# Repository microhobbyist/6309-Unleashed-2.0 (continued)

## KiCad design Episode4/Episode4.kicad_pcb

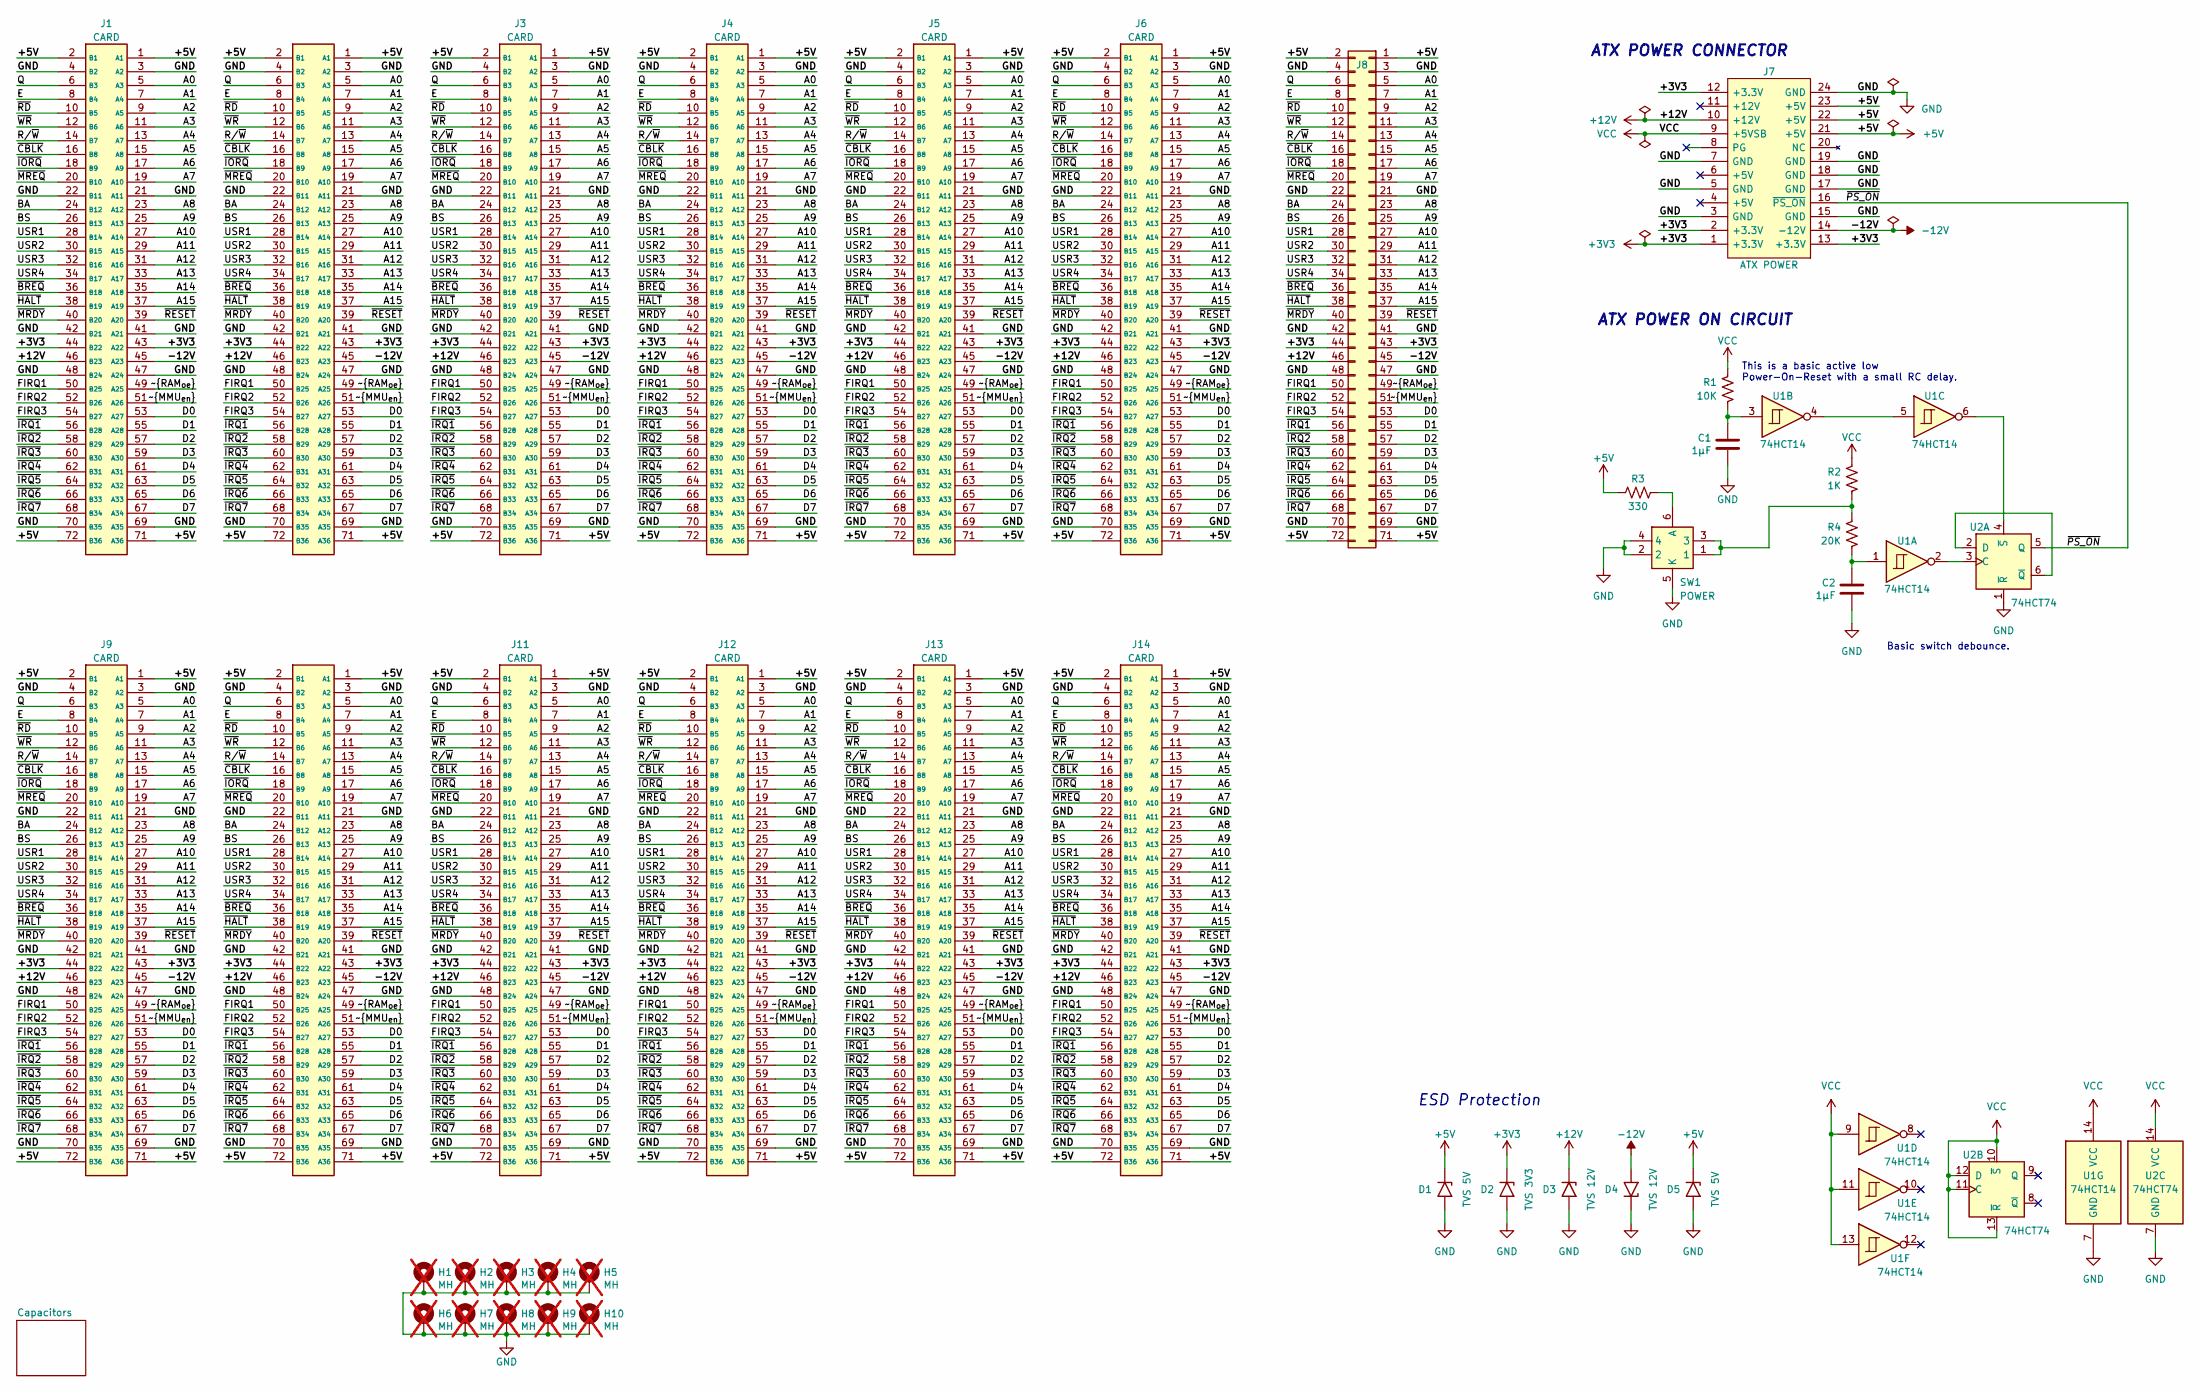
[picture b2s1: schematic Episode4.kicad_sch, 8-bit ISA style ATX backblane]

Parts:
C1, C2: 1µF; C_0805_2012Metric_Pad1.18x1.45mm_HandSolder; Manufacturer_Part_Number CL21B105KBFNNNG
D1, D5: TVS 5V; D_SMB; Manufacturer_Part_Number SMBJ5.0A-E3/5B
D2: TVS 3V3; D_SMB; Manufacturer_Part_Number SMBJ3V3-E3/5B
D3, D4: TVS 12V; D_SMB; Manufacturer_Part_Number SMBJ12A-E3/5B
H1, H2, H3, H4, H5, H6, H7, H8, H9, H10: MH; MountingHole_3.5mm_Pad_Via; not fitted
J1, J2, J3, J4, J5, J6, J9, J10, J11, J12, J13, J14: CARD; 72-pin CE connector; Mouser Part Number 571-5530843-8
J7: ATX POWER; ATX_PSU_CONN; Mouser Part Number 571-1-1775099-3
J8: BB Con; PinSocket_2x36_P2.54mm_Vertical; Manufacturer_Part_Number 929852-01-36-RA
R1: 10K; R_0805_2012Metric_Pad1.20x1.40mm_HandSolder; Manufacturer_Part_Number CR0805-FX-1002ELF
R2: 1K; R_0805_2012Metric_Pad1.20x1.40mm_HandSolder; Manufacturer_Part_Number CR0805-FX-1001ELF
R3: 330; R_0805_2012Metric_Pad1.20x1.40mm_HandSolder; Manufacturer_Part_Number CR0805-FX-3300ELF
R4: 20K; R_0805_2012Metric_Pad1.20x1.40mm_HandSolder; Manufacturer_Part_Number CR0805-FX-2002ELF
SW1: POWER; TS2912121G300D; Manufacturer_Part_Number TS29-1212-1-G-300-D; Mouser Part Number 179-TS2912121G300D
U1: 74HCT14; SOIC-14_3.9x8.7mm_P1.27mm; Manufacturer_Part_Number CD74HCT14M96
U2: 74HCT74; SOIC-14_3.9x8.7mm_P1.27mm; Manufacturer_Part_Number CD74HCT74M96

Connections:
+3V3: D2.1 (A1), J1.43 (A22), J1.44 (B22), J2.43 (A22), J2.44 (B22), J3.43 (A22), J3.44 (B22), J4.43 (A22), J4.44 (B22), J5.43 (A22), J5.44 (B22), J6.43 (A22), J6.44 (B22), J7.1 (+3.3V), J7.2 (+3.3V), J7.12 (+3.3V), J7.13 (+3.3V), J8.43, J8.44, J9.43 (A22), J9.44 (B22), J10.43 (A22), J10.44 (B22), J11.43 (A22), J11.44 (B22), J12.43 (A22), J12.44 (B22), J13.43 (A22), J13.44 (B22), J14.43 (A22), J14.44 (B22); also elsewhere on the board
+5V: D1.1 (A1), D5.1 (A1), J1.1 (A1), J1.2 (B1), J1.71 (A36), J1.72 (B36), J2.1 (A1), J2.2 (B1), J2.71 (A36), J2.72 (B36), J3.1 (A1), J3.2 (B1), J3.71 (A36), J3.72 (B36), J4.1 (A1), J4.2 (B1), J4.71 (A36), J4.72 (B36), J5.1 (A1), J5.2 (B1), J5.71 (A36), J5.72 (B36), J6.1 (A1), J6.2 (B1), J6.71 (A36), J6.72 (B36), J7.21 (+5V), J7.22 (+5V), J7.23 (+5V), J8.1, J8.2, J8.71, J8.72, J9.1 (A1), J9.2 (B1), J9.71 (A36), J9.72 (B36), J10.1 (A1), J10.2 (B1), J10.71 (A36), J10.72 (B36), J11.1 (A1), J11.2 (B1), J11.71 (A36), J11.72 (B36), J12.1 (A1), J12.2 (B1), J12.71 (A36), J12.72 (B36), J13.1 (A1), J13.2 (B1), J13.71 (A36), J13.72 (B36), J14.1 (A1), J14.2 (B1), J14.71 (A36), J14.72 (B36), R3.2; also elsewhere on the board
+12V: D3.1 (A1), J1.46 (B23), J2.46 (B23), J3.46 (B23), J4.46 (B23), J5.46 (B23), J6.46 (B23), J7.10 (+12V), J8.46, J9.46 (B23), J10.46 (B23), J11.46 (B23), J12.46 (B23), J13.46 (B23), J14.46 (B23); also elsewhere on the board
-12V: D4.2 (A2), J1.45 (A23), J2.45 (A23), J3.45 (A23), J4.45 (A23), J5.45 (A23), J6.45 (A23), J7.14 (-12V), J8.45, J9.45 (A23), J10.45 (A23), J11.45 (A23), J12.45 (A23), J13.45 (A23), J14.45 (A23); also elsewhere on the board
/A0: J1.5 (A3), J2.5 (A3), J3.5 (A3), J4.5 (A3), J5.5 (A3), J6.5 (A3), J8.5, J9.5 (A3), J10.5 (A3), J11.5 (A3), J12.5 (A3), J13.5 (A3), J14.5 (A3)
/A1: J1.7 (A4), J2.7 (A4), J3.7 (A4), J4.7 (A4), J5.7 (A4), J6.7 (A4), J8.7, J9.7 (A4), J10.7 (A4), J11.7 (A4), J12.7 (A4), J13.7 (A4), J14.7 (A4)
/A2: J1.9 (A5), J2.9 (A5), J3.9 (A5), J4.9 (A5), J5.9 (A5), J6.9 (A5), J8.9, J9.9 (A5), J10.9 (A5), J11.9 (A5), J12.9 (A5), J13.9 (A5), J14.9 (A5)
/A3: J1.11 (A6), J2.11 (A6), J3.11 (A6), J4.11 (A6), J5.11 (A6), J6.11 (A6), J8.11, J9.11 (A6), J10.11 (A6), J11.11 (A6), J12.11 (A6), J13.11 (A6), J14.11 (A6)
/A4: J1.13 (A7), J2.13 (A7), J3.13 (A7), J4.13 (A7), J5.13 (A7), J6.13 (A7), J8.13, J9.13 (A7), J10.13 (A7), J11.13 (A7), J12.13 (A7), J13.13 (A7), J14.13 (A7)
/A5: J1.15 (A8), J2.15 (A8), J3.15 (A8), J4.15 (A8), J5.15 (A8), J6.15 (A8), J8.15, J9.15 (A8), J10.15 (A8), J11.15 (A8), J12.15 (A8), J13.15 (A8), J14.15 (A8)
/A6: J1.17 (A9), J2.17 (A9), J3.17 (A9), J4.17 (A9), J5.17 (A9), J6.17 (A9), J8.17, J9.17 (A9), J10.17 (A9), J11.17 (A9), J12.17 (A9), J13.17 (A9), J14.17 (A9)
/A7: J1.19 (A10), J2.19 (A10), J3.19 (A10), J4.19 (A10), J5.19 (A10), J6.19 (A10), J8.19, J9.19 (A10), J10.19 (A10), J11.19 (A10), J12.19 (A10), J13.19 (A10), J14.19 (A10)
/A8: J1.23 (A12), J2.23 (A12), J3.23 (A12), J4.23 (A12), J5.23 (A12), J6.23 (A12), J8.23, J9.23 (A12), J10.23 (A12), J11.23 (A12), J12.23 (A12), J13.23 (A12), J14.23 (A12)
/A9: J1.25 (A13), J2.25 (A13), J3.25 (A13), J4.25 (A13), J5.25 (A13), J6.25 (A13), J8.25, J9.25 (A13), J10.25 (A13), J11.25 (A13), J12.25 (A13), J13.25 (A13), J14.25 (A13)
/A10: J1.27 (A14), J2.27 (A14), J3.27 (A14), J4.27 (A14), J5.27 (A14), J6.27 (A14), J8.27, J9.27 (A14), J10.27 (A14), J11.27 (A14), J12.27 (A14), J13.27 (A14), J14.27 (A14)
/A11: J1.29 (A15), J2.29 (A15), J3.29 (A15), J4.29 (A15), J5.29 (A15), J6.29 (A15), J8.29, J9.29 (A15), J10.29 (A15), J11.29 (A15), J12.29 (A15), J13.29 (A15), J14.29 (A15)
/A12: J1.31 (A16), J2.31 (A16), J3.31 (A16), J4.31 (A16), J5.31 (A16), J6.31 (A16), J8.31, J9.31 (A16), J10.31 (A16), J11.31 (A16), J12.31 (A16), J13.31 (A16), J14.31 (A16)
/A13: J1.33 (A17), J2.33 (A17), J3.33 (A17), J4.33 (A17), J5.33 (A17), J6.33 (A17), J8.33, J9.33 (A17), J10.33 (A17), J11.33 (A17), J12.33 (A17), J13.33 (A17), J14.33 (A17)
/A14: J1.35 (A18), J2.35 (A18), J3.35 (A18), J4.35 (A18), J5.35 (A18), J6.35 (A18), J8.35, J9.35 (A18), J10.35 (A18), J11.35 (A18), J12.35 (A18), J13.35 (A18), J14.35 (A18)
/A15: J1.37 (A19), J2.37 (A19), J3.37 (A19), J4.37 (A19), J5.37 (A19), J6.37 (A19), J8.37, J9.37 (A19), J10.37 (A19), J11.37 (A19), J12.37 (A19), J13.37 (A19), J14.37 (A19)
/BA: J1.24 (B12), J2.24 (B12), J3.24 (B12), J4.24 (B12), J5.24 (B12), J6.24 (B12), J8.24, J9.24 (B12), J10.24 (B12), J11.24 (B12), J12.24 (B12), J13.24 (B12), J14.24 (B12)
/BS: J1.26 (B13), J2.26 (B13), J3.26 (B13), J4.26 (B13), J5.26 (B13), J6.26 (B13), J8.26, J9.26 (B13), J10.26 (B13), J11.26 (B13), J12.26 (B13), J13.26 (B13), J14.26 (B13)
/D0: J1.53 (A27), J2.53 (A27), J3.53 (A27), J4.53 (A27), J5.53 (A27), J6.53 (A27), J8.53, J9.53 (A27), J10.53 (A27), J11.53 (A27), J12.53 (A27), J13.53 (A27), J14.53 (A27)
/D1: J1.55 (A28), J2.55 (A28), J3.55 (A28), J4.55 (A28), J5.55 (A28), J6.55 (A28), J8.55, J9.55 (A28), J10.55 (A28), J11.55 (A28), J12.55 (A28), J13.55 (A28), J14.55 (A28)
/D2: J1.57 (A29), J2.57 (A29), J3.57 (A29), J4.57 (A29), J5.57 (A29), J6.57 (A29), J8.57, J9.57 (A29), J10.57 (A29), J11.57 (A29), J12.57 (A29), J13.57 (A29), J14.57 (A29)
/D3: J1.59 (A30), J2.59 (A30), J3.59 (A30), J4.59 (A30), J5.59 (A30), J6.59 (A30), J8.59, J9.59 (A30), J10.59 (A30), J11.59 (A30), J12.59 (A30), J13.59 (A30), J14.59 (A30)
/D4: J1.61 (A31), J2.61 (A31), J3.61 (A31), J4.61 (A31), J5.61 (A31), J6.61 (A31), J8.61, J9.61 (A31), J10.61 (A31), J11.61 (A31), J12.61 (A31), J13.61 (A31), J14.61 (A31)
/D5: J1.63 (A32), J2.63 (A32), J3.63 (A32), J4.63 (A32), J5.63 (A32), J6.63 (A32), J8.63, J9.63 (A32), J10.63 (A32), J11.63 (A32), J12.63 (A32), J13.63 (A32), J14.63 (A32)
/D6: J1.65 (A33), J2.65 (A33), J3.65 (A33), J4.65 (A33), J5.65 (A33), J6.65 (A33), J8.65, J9.65 (A33), J10.65 (A33), J11.65 (A33), J12.65 (A33), J13.65 (A33), J14.65 (A33)
/D7: J1.67 (A34), J2.67 (A34), J3.67 (A34), J4.67 (A34), J5.67 (A34), J6.67 (A34), J8.67, J9.67 (A34), J10.67 (A34), J11.67 (A34), J12.67 (A34), J13.67 (A34), J14.67 (A34)
/E: J1.8 (B4), J2.8 (B4), J3.8 (B4), J4.8 (B4), J5.8 (B4), J6.8 (B4), J8.8, J9.8 (B4), J10.8 (B4), J11.8 (B4), J12.8 (B4), J13.8 (B4), J14.8 (B4)
/FIRQ1: J1.50 (B25), J2.50 (B25), J3.50 (B25), J4.50 (B25), J5.50 (B25), J6.50 (B25), J8.50, J9.50 (B25), J10.50 (B25), J11.50 (B25), J12.50 (B25), J13.50 (B25), J14.50 (B25)
/FIRQ2: J1.52 (B26), J2.52 (B26), J3.52 (B26), J4.52 (B26), J5.52 (B26), J6.52 (B26), J8.52, J9.52 (B26), J10.52 (B26), J11.52 (B26), J12.52 (B26), J13.52 (B26), J14.52 (B26)
/FIRQ3: J1.54 (B27), J2.54 (B27), J3.54 (B27), J4.54 (B27), J5.54 (B27), J6.54 (B27), J8.54, J9.54 (B27), J10.54 (B27), J11.54 (B27), J12.54 (B27), J13.54 (B27), J14.54 (B27)
/Q: J1.6 (B3), J2.6 (B3), J3.6 (B3), J4.6 (B3), J5.6 (B3), J6.6 (B3), J8.6, J9.6 (B3), J10.6 (B3), J11.6 (B3), J12.6 (B3), J13.6 (B3), J14.6 (B3)
/R/~W: J1.14 (B7), J2.14 (B7), J3.14 (B7), J4.14 (B7), J5.14 (B7), J6.14 (B7), J8.14, J9.14 (B7), J10.14 (B7), J11.14 (B7), J12.14 (B7), J13.14 (B7), J14.14 (B7)
/USR1: J1.28 (B14), J2.28 (B14), J3.28 (B14), J4.28 (B14), J5.28 (B14), J6.28 (B14), J8.28, J9.28 (B14), J10.28 (B14), J11.28 (B14), J12.28 (B14), J13.28 (B14), J14.28 (B14)
/USR2: J1.30 (B15), J2.30 (B15), J3.30 (B15), J4.30 (B15), J5.30 (B15), J6.30 (B15), J8.30, J9.30 (B15), J10.30 (B15), J11.30 (B15), J12.30 (B15), J13.30 (B15), J14.30 (B15)
/USR3: J1.32 (B16), J2.32 (B16), J3.32 (B16), J4.32 (B16), J5.32 (B16), J6.32 (B16), J8.32, J9.32 (B16), J10.32 (B16), J11.32 (B16), J12.32 (B16), J13.32 (B16), J14.32 (B16)
/USR4: J1.34 (B17), J2.34 (B17), J3.34 (B17), J4.34 (B17), J5.34 (B17), J6.34 (B17), J8.34, J9.34 (B17), J10.34 (B17), J11.34 (B17), J12.34 (B17), J13.34 (B17), J14.34 (B17)
/~BREQ: J1.36 (B18), J2.36 (B18), J3.36 (B18), J4.36 (B18), J5.36 (B18), J6.36 (B18), J8.36, J9.36 (B18), J10.36 (B18), J11.36 (B18), J12.36 (B18), J13.36 (B18), J14.36 (B18)
/~CBLK: J1.16 (B8), J2.16 (B8), J3.16 (B8), J4.16 (B8), J5.16 (B8), J6.16 (B8), J8.16, J9.16 (B8), J10.16 (B8), J11.16 (B8), J12.16 (B8), J13.16 (B8), J14.16 (B8)
/~HALT: J1.38 (B19), J2.38 (B19), J3.38 (B19), J4.38 (B19), J5.38 (B19), J6.38 (B19), J8.38, J9.38 (B19), J10.38 (B19), J11.38 (B19), J12.38 (B19), J13.38 (B19), J14.38 (B19)
/~IORQ: J1.18 (B9), J2.18 (B9), J3.18 (B9), J4.18 (B9), J5.18 (B9), J6.18 (B9), J8.18, J9.18 (B9), J10.18 (B9), J11.18 (B9), J12.18 (B9), J13.18 (B9), J14.18 (B9)
/~IRQ1: J1.56 (B28), J2.56 (B28), J3.56 (B28), J4.56 (B28), J5.56 (B28), J6.56 (B28), J8.56, J9.56 (B28), J10.56 (B28), J11.56 (B28), J12.56 (B28), J13.56 (B28), J14.56 (B28)
/~IRQ2: J1.58 (B29), J2.58 (B29), J3.58 (B29), J4.58 (B29), J5.58 (B29), J6.58 (B29), J8.58, J9.58 (B29), J10.58 (B29), J11.58 (B29), J12.58 (B29), J13.58 (B29), J14.58 (B29)
/~IRQ3: J1.60 (B30), J2.60 (B30), J3.60 (B30), J4.60 (B30), J5.60 (B30), J6.60 (B30), J8.60, J9.60 (B30), J10.60 (B30), J11.60 (B30), J12.60 (B30), J13.60 (B30), J14.60 (B30)
/~IRQ4: J1.62 (B31), J2.62 (B31), J3.62 (B31), J4.62 (B31), J5.62 (B31), J6.62 (B31), J8.62, J9.62 (B31), J10.62 (B31), J11.62 (B31), J12.62 (B31), J13.62 (B31), J14.62 (B31)
/~IRQ5: J1.64 (B32), J2.64 (B32), J3.64 (B32), J4.64 (B32), J5.64 (B32), J6.64 (B32), J8.64, J9.64 (B32), J10.64 (B32), J11.64 (B32), J12.64 (B32), J13.64 (B32), J14.64 (B32)
/~IRQ6: J1.66 (B33), J2.66 (B33), J3.66 (B33), J4.66 (B33), J5.66 (B33), J6.66 (B33), J8.66, J9.66 (B33), J10.66 (B33), J11.66 (B33), J12.66 (B33), J13.66 (B33), J14.66 (B33)
/~IRQ7: J1.68 (B34), J2.68 (B34), J3.68 (B34), J4.68 (B34), J5.68 (B34), J6.68 (B34), J8.68, J9.68 (B34), J10.68 (B34), J11.68 (B34), J12.68 (B34), J13.68 (B34), J14.68 (B34)
/~MMU_{en}: J1.51 (A26), J2.51 (A26), J3.51 (A26), J4.51 (A26), J5.51 (A26), J6.51 (A26), J8.51, J9.51 (A26), J10.51 (A26), J11.51 (A26), J12.51 (A26), J13.51 (A26), J14.51 (A26)
/~MRDY: J1.40 (B20), J2.40 (B20), J3.40 (B20), J4.40 (B20), J5.40 (B20), J6.40 (B20), J8.40, J9.40 (B20), J10.40 (B20), J11.40 (B20), J12.40 (B20), J13.40 (B20), J14.40 (B20)
/~MREQ: J1.20 (B10), J2.20 (B10), J3.20 (B10), J4.20 (B10), J5.20 (B10), J6.20 (B10), J8.20, J9.20 (B10), J10.20 (B10), J11.20 (B10), J12.20 (B10), J13.20 (B10), J14.20 (B10)
/~PS_ON: J7.16 (~PS_ON), U2.5 (Q)
/~RAM_{oe}: J1.49 (A25), J2.49 (A25), J3.49 (A25), J4.49 (A25), J5.49 (A25), J6.49 (A25), J8.49, J9.49 (A25), J10.49 (A25), J11.49 (A25), J12.49 (A25), J13.49 (A25), J14.49 (A25)
/~RD: J1.10 (B5), J2.10 (B5), J3.10 (B5), J4.10 (B5), J5.10 (B5), J6.10 (B5), J8.10, J9.10 (B5), J10.10 (B5), J11.10 (B5), J12.10 (B5), J13.10 (B5), J14.10 (B5)
/~RESET: J1.39 (A20), J2.39 (A20), J3.39 (A20), J4.39 (A20), J5.39 (A20), J6.39 (A20), J8.39, J9.39 (A20), J10.39 (A20), J11.39 (A20), J12.39 (A20), J13.39 (A20), J14.39 (A20)
/~WR: J1.12 (B6), J2.12 (B6), J3.12 (B6), J4.12 (B6), J5.12 (B6), J6.12 (B6), J8.12, J9.12 (B6), J10.12 (B6), J11.12 (B6), J12.12 (B6), J13.12 (B6), J14.12 (B6)
GND: C1.2, C2.2, D1.2 (A2), D2.2 (A2), D3.2 (A2), D4.1 (A1), D5.2 (A2), H1.1, H2.1, H3.1, H4.1, H5.1, H6.1, H7.1, H8.1, H9.1, H10.1, J1.3 (A2), J1.4 (B2), J1.21 (A11), J1.22 (B11), J1.41 (A21), J1.42 (B21), J1.47 (A24), J1.48 (B24), J1.69 (A35), J1.70 (B35), J2.3 (A2), J2.4 (B2), J2.21 (A11), J2.22 (B11), J2.41 (A21), J2.42 (B21), J2.47 (A24), J2.48 (B24), J2.69 (A35), J2.70 (B35), J3.3 (A2), J3.4 (B2), J3.21 (A11), J3.22 (B11), J3.41 (A21), J3.42 (B21), J3.47 (A24), J3.48 (B24), J3.69 (A35), J3.70 (B35), J4.3 (A2), J4.4 (B2), J4.21 (A11), J4.22 (B11), J4.41 (A21), J4.42 (B21), J4.47 (A24), J4.48 (B24), J4.69 (A35), J4.70 (B35), J5.3 (A2), J5.4 (B2), J5.21 (A11), J5.22 (B11), J5.41 (A21), J5.42 (B21), J5.47 (A24), J5.48 (B24), J5.69 (A35), J5.70 (B35), J6.3 (A2), J6.4 (B2), J6.21 (A11), J6.22 (B11), J6.41 (A21), J6.42 (B21), J6.47 (A24), J6.48 (B24), J6.69 (A35), J6.70 (B35), J7.3 (GND), J7.5 (GND), J7.7 (GND), J7.15 (GND), J7.17 (GND), J7.18 (GND), J7.19 (GND), J7.24 (GND), J8.3, J8.4, J8.21, J8.22, J8.41, J8.42, J8.47, J8.48, J8.69, J8.70, J9.3 (A2), J9.4 (B2), J9.21 (A11), J9.22 (B11), J9.41 (A21), J9.42 (B21), J9.47 (A24), J9.48 (B24), J9.69 (A35), J9.70 (B35), J10.3 (A2), J10.4 (B2), J10.21 (A11), J10.22 (B11), J10.41 (A21), J10.42 (B21), J10.47 (A24), J10.48 (B24), J10.69 (A35), J10.70 (B35), J11.3 (A2), J11.4 (B2), J11.21 (A11), J11.22 (B11), J11.41 (A21), J11.42 (B21), J11.47 (A24), J11.48 (B24), J11.69 (A35), J11.70 (B35), J12.3 (A2), J12.4 (B2), J12.21 (A11), J12.22 (B11), J12.41 (A21), J12.42 (B21), J12.47 (A24), J12.48 (B24), J12.69 (A35), J12.70 (B35), J13.3 (A2), J13.4 (B2), J13.21 (A11), J13.22 (B11), J13.41 (A21), J13.42 (B21), J13.47 (A24), J13.48 (B24), J13.69 (A35), J13.70 (B35), J14.3 (A2), J14.4 (B2), J14.21 (A11), J14.22 (B11), J14.41 (A21), J14.42 (B21), J14.47 (A24), J14.48 (B24), J14.69 (A35), J14.70 (B35), SW1.2, SW1.4, SW1.5 (K), U1.7 (GND), U2.1 (~R), U2.7 (GND); also elsewhere on the board
unnamed: C1.1, R1.2, U1.3
unnamed: C2.1, R4.2, U1.1
unnamed: R2.2, R4.1, SW1.1, SW1.3
unnamed: R3.1, SW1.6 (A)
unnamed: U1.4, U1.5
unnamed: U1.2, U2.3 (C)
unnamed: U2.2 (D), U2.6 (~Q)
unnamed: U1.6, U2.4 (~S)
VCC: J7.9 (+5VSB), R1.1, R2.1, U1.9, U1.11, U1.13, U1.14 (VCC), U2.10 (~S), U2.11 (C), U2.12 (D), U2.13 (~R), U2.14 (VCC); also elsewhere on the board

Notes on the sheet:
ATX POWER CONNECTOR
This is a basic active low Power-On-Reset with a small RC delay.
Basic switch debounce.
ATX POWER ON CIRCUIT
ESD Protection

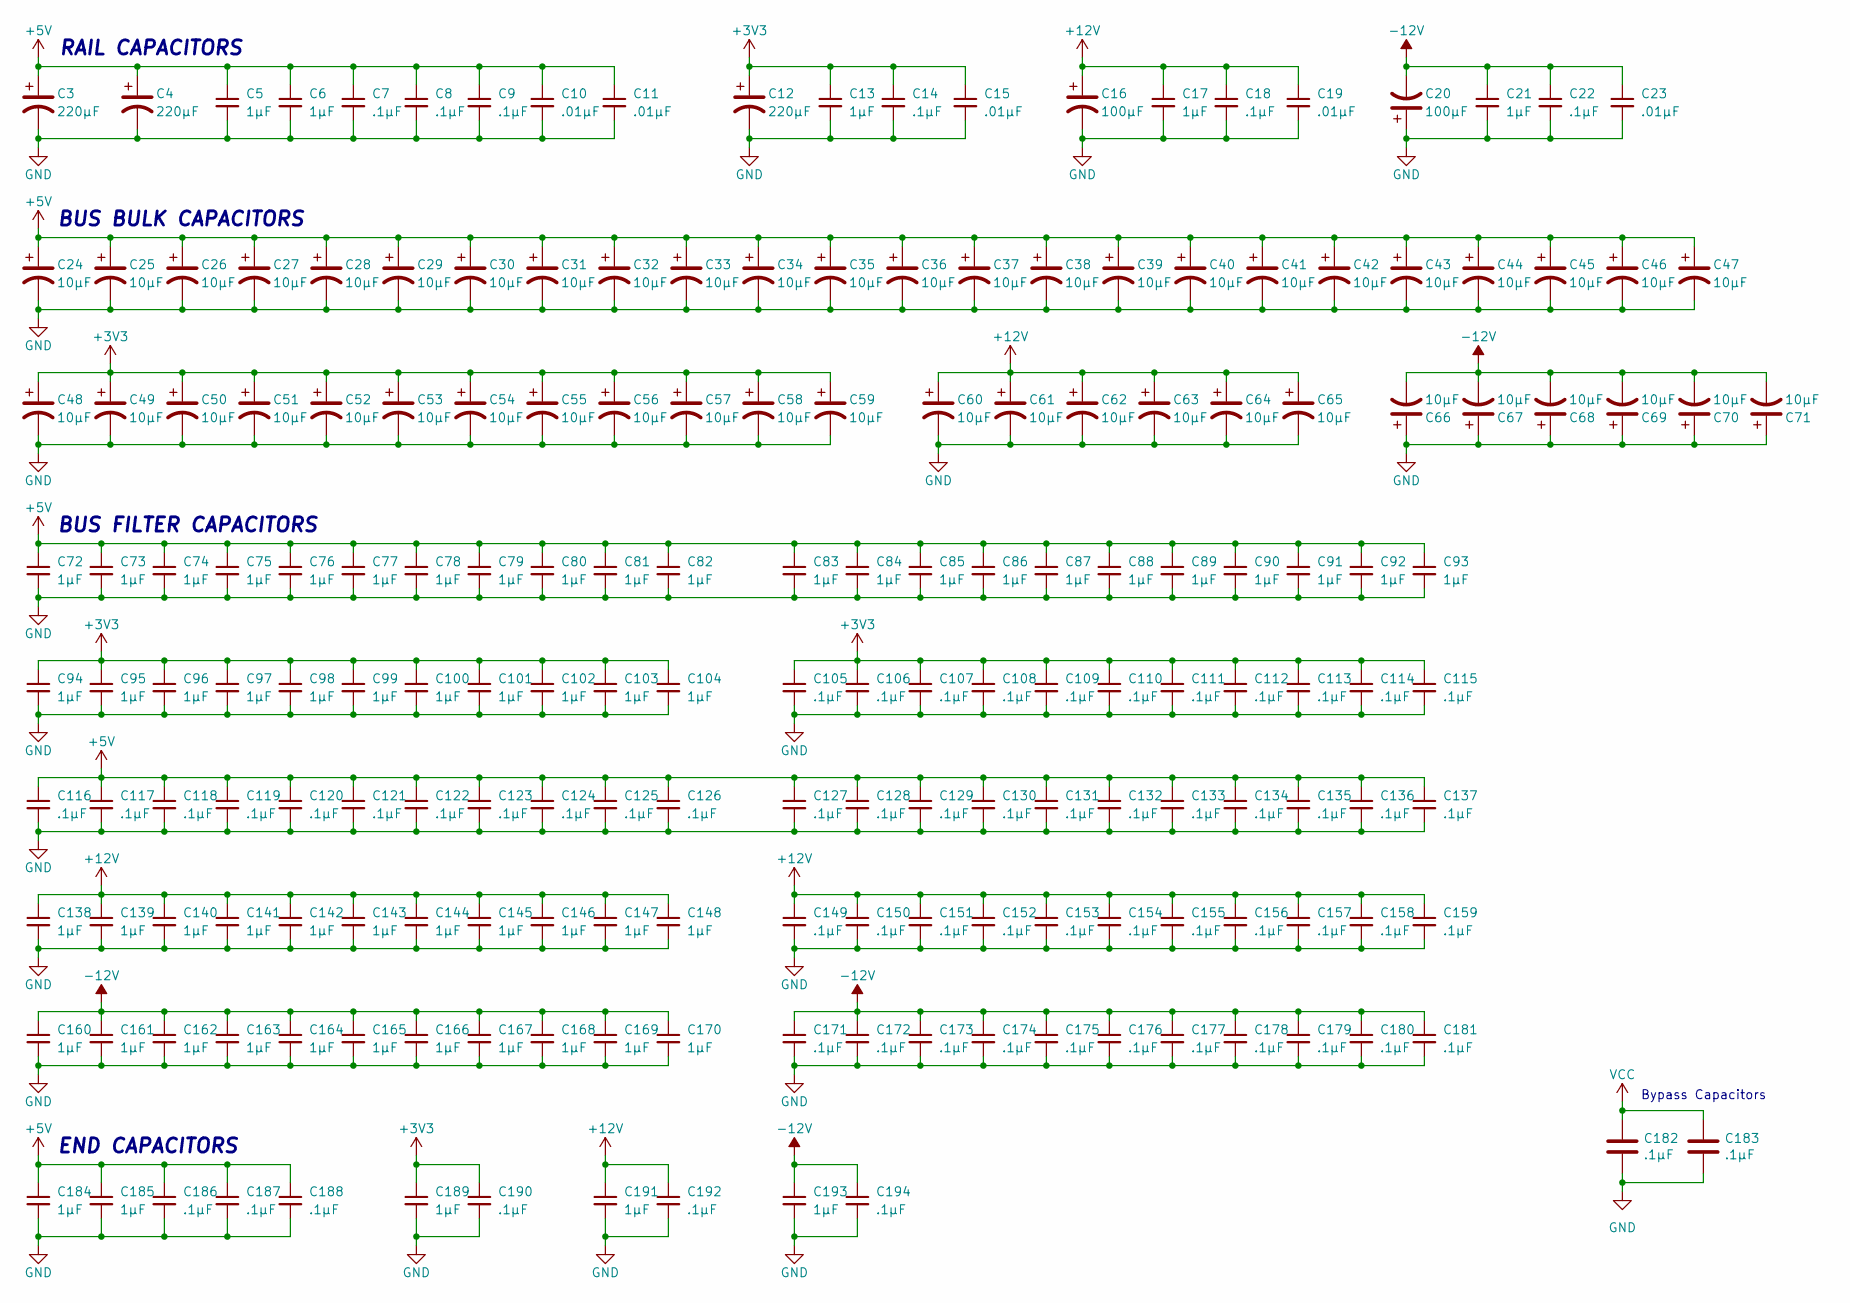
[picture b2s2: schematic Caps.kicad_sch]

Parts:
C3, C4, C12: 220µF; CP_Elec_6.3x7.7; Manufacturer_Part_Number UCD1C221MCL1GS
C5, C6, C13, C17, C21, C72, C73, C74, C75, C76, C77, C78, C79, C80, C81, C82, C83, C84, C85, C86, C87, C88, C89, C90, C91, C92, C93, C94, C95, C96, C97, C98, C99, C100, C101, C102, C103, C104, C138, C139, C140, C141, C142, C143, C144, C145, C146, C147, C148, C160, C161, C162, C163, C164, C165, C166, C167, C168, C169, C170, C184, C185, C189, C191, C193: 1µF; C_0805_2012Metric_Pad1.18x1.45mm_HandSolder; Manufacturer_Part_Number CL21B105KBFNNNG
C7, C8, C9, C14, C18, C22, C105, C106, C107, C108, C109, C110, C111, C112, C113, C114, C115, C116, C117, C118, C119, C120, C121, C122, C123, C124, C125, C126, C127, C128, C129, C130, C131, C132, C133, C134, C135, C136, C137, C149, C150, C151, C152, C153, C154, C155, C156, C157, C158, C159, C171, C172, C173, C174, C175, C176, C177, C178, C179, C180, C181, C182, C183, C186, C187, C188, C190, C192, C194: .1µF; C_0805_2012Metric_Pad1.18x1.45mm_HandSolder; Manufacturer_Part_Number CL21B104KBFNNNG
C10, C11, C15, C19, C23: .01µF; C_0805_2012Metric_Pad1.18x1.45mm_HandSolder; Manufacturer_Part_Number CL21B103KBCNNNC
C16, C20: 100µF; CP_Elec_6.3x7.7; Manufacturer_Part_Number UCD1E101MCL1GS
C24, C25, C26, C27, C28, C29, C30, C31, C32, C33, C34, C35, C36, C37, C38, C39, C40, C41, C42, C43, C44, C45, C46, C47, C48, C49, C50, C51, C52, C53, C54, C55, C56, C57, C58, C59, C60, C61, C62, C63, C64, C65, C66, C67, C68, C69, C70, C71: 10µF; CP_Elec_4x5.8; Manufacturer_Part_Number UCD1E100MCL1GS

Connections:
+3V3: C12.1, C13.1, C14.1, C15.1, C48.1, C49.1, C50.1, C51.1, C52.1, C53.1, C54.1, C55.1, C56.1, C57.1, C58.1, C59.1, C94.1, C95.1, C96.1, C97.1, C98.1, C99.1, C100.1, C101.1, C102.1, C103.1, C104.1, C105.1, C106.1, C107.1, C108.1, C109.1, C110.1, C111.1, C112.1, C113.1, C114.1, C115.1, C189.1, C190.1; also elsewhere on the board
+5V: C3.1, C4.1, C5.1, C6.1, C7.1, C8.1, C9.1, C10.1, C11.1, C24.1, C25.1, C26.1, C27.1, C28.1, C29.1, C30.1, C31.1, C32.1, C33.1, C34.1, C35.1, C36.1, C37.1, C38.1, C39.1, C40.1, C41.1, C42.1, C43.1, C44.1, C45.1, C46.1, C47.1, C72.1, C73.1, C74.1, C75.1, C76.1, C77.1, C78.1, C79.1, C80.1, C81.1, C82.1, C83.1, C84.1, C85.1, C86.1, C87.1, C88.1, C89.1, C90.1, C91.1, C92.1, C93.1, C116.1, C117.1, C118.1, C119.1, C120.1, C121.1, C122.1, C123.1, C124.1, C125.1, C126.1, C127.1, C128.1, C129.1, C130.1, C131.1, C132.1, C133.1, C134.1, C135.1, C136.1, C137.1, C184.1, C185.1, C186.1, C187.1, C188.1; also elsewhere on the board
+12V: C16.1, C17.1, C18.1, C19.1, C60.1, C61.1, C62.1, C63.1, C64.1, C65.1, C138.1, C139.1, C140.1, C141.1, C142.1, C143.1, C144.1, C145.1, C146.1, C147.1, C148.1, C149.1, C150.1, C151.1, C152.1, C153.1, C154.1, C155.1, C156.1, C157.1, C158.1, C159.1, C191.1, C192.1; also elsewhere on the board
-12V: C20.2, C21.1, C22.1, C23.1, C66.2, C67.2, C68.2, C69.2, C70.2, C71.2, C160.1, C161.1, C162.1, C163.1, C164.1, C165.1, C166.1, C167.1, C168.1, C169.1, C170.1, C171.1, C172.1, C173.1, C174.1, C175.1, C176.1, C177.1, C178.1, C179.1, C180.1, C181.1, C193.1, C194.1; also elsewhere on the board
GND: C3.2, C4.2, C5.2, C6.2, C7.2, C8.2, C9.2, C10.2, C11.2, C12.2, C13.2, C14.2, C15.2, C16.2, C17.2, C18.2, C19.2, C20.1, C21.2, C22.2, C23.2, C24.2, C25.2, C26.2, C27.2, C28.2, C29.2, C30.2, C31.2, C32.2, C33.2, C34.2, C35.2, C36.2, C37.2, C38.2, C39.2, C40.2, C41.2, C42.2, C43.2, C44.2, C45.2, C46.2, C47.2, C48.2, C49.2, C50.2, C51.2, C52.2, C53.2, C54.2, C55.2, C56.2, C57.2, C58.2, C59.2, C60.2, C61.2, C62.2, C63.2, C64.2, C65.2, C66.1, C67.1, C68.1, C69.1, C70.1, C71.1, C72.2, C73.2, C74.2, C75.2, C76.2, C77.2, C78.2, C79.2, C80.2, C81.2, C82.2, C83.2, C84.2, C85.2, C86.2, C87.2, C88.2, C89.2, C90.2, C91.2, C92.2, C93.2, C94.2, C95.2, C96.2, C97.2, C98.2, C99.2, C100.2, C101.2, C102.2, C103.2, C104.2, C105.2, C106.2, C107.2, C108.2, C109.2, C110.2, C111.2, C112.2, C113.2, C114.2, C115.2, C116.2, C117.2, C118.2, C119.2, C120.2, C121.2, C122.2, C123.2, C124.2, C125.2, C126.2, C127.2, C128.2, C129.2, C130.2, C131.2, C132.2, C133.2, C134.2, C135.2, C136.2, C137.2, C138.2, C139.2, C140.2, C141.2, C142.2, C143.2, C144.2, C145.2, C146.2, C147.2, C148.2, C149.2, C150.2, C151.2, C152.2, C153.2, C154.2, C155.2, C156.2, C157.2, C158.2, C159.2, C160.2, C161.2, C162.2, C163.2, C164.2, C165.2, C166.2, C167.2, C168.2, C169.2, C170.2, C171.2, C172.2, C173.2, C174.2, C175.2, C176.2, C177.2, C178.2, C179.2, C180.2, C181.2, C182.2, C183.2, C184.2, C185.2, C186.2, C187.2, C188.2, C189.2, C190.2, C191.2, C192.2, C193.2, C194.2; also elsewhere on the board
VCC: C182.1, C183.1; also elsewhere on the board

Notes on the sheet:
BUS BULK CAPACITORS
END CAPACITORS
RAIL CAPACITORS
Bypass Capacitors
BUS FILTER CAPACITORS

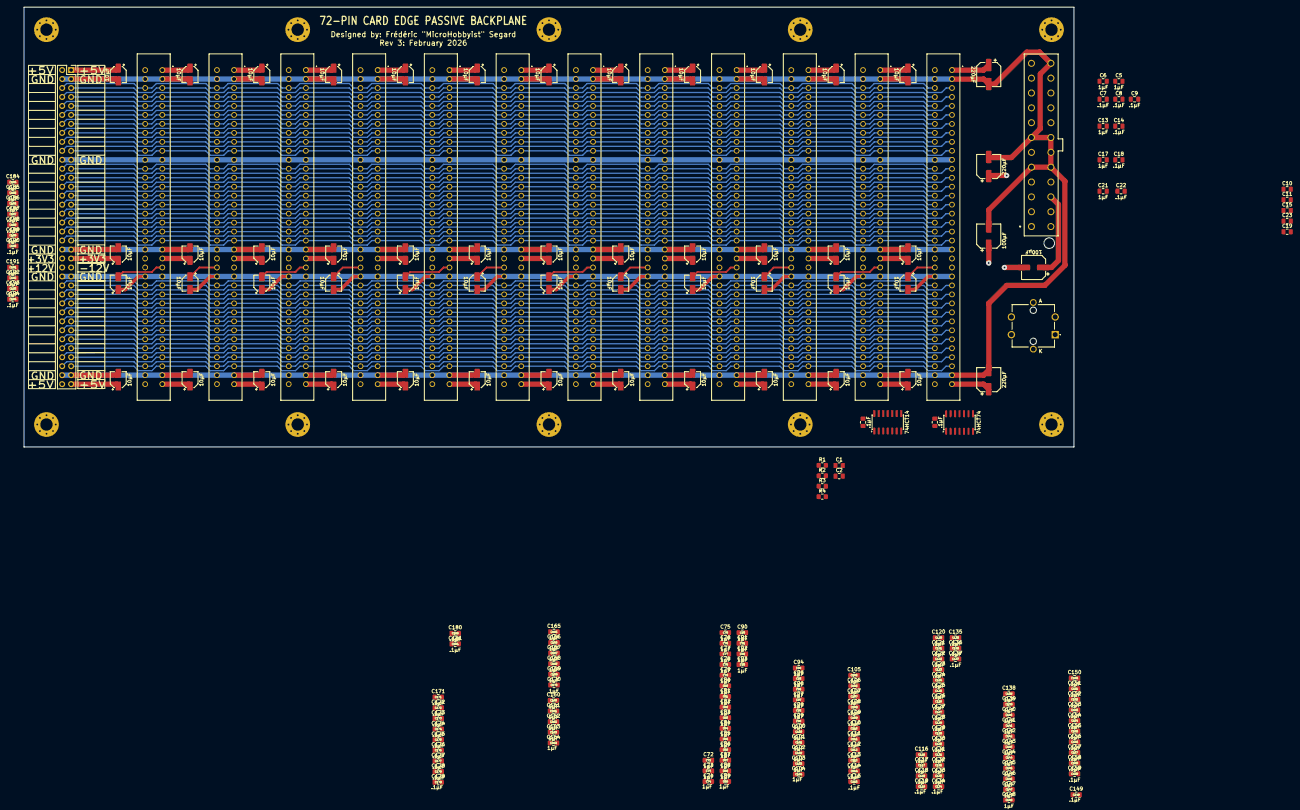
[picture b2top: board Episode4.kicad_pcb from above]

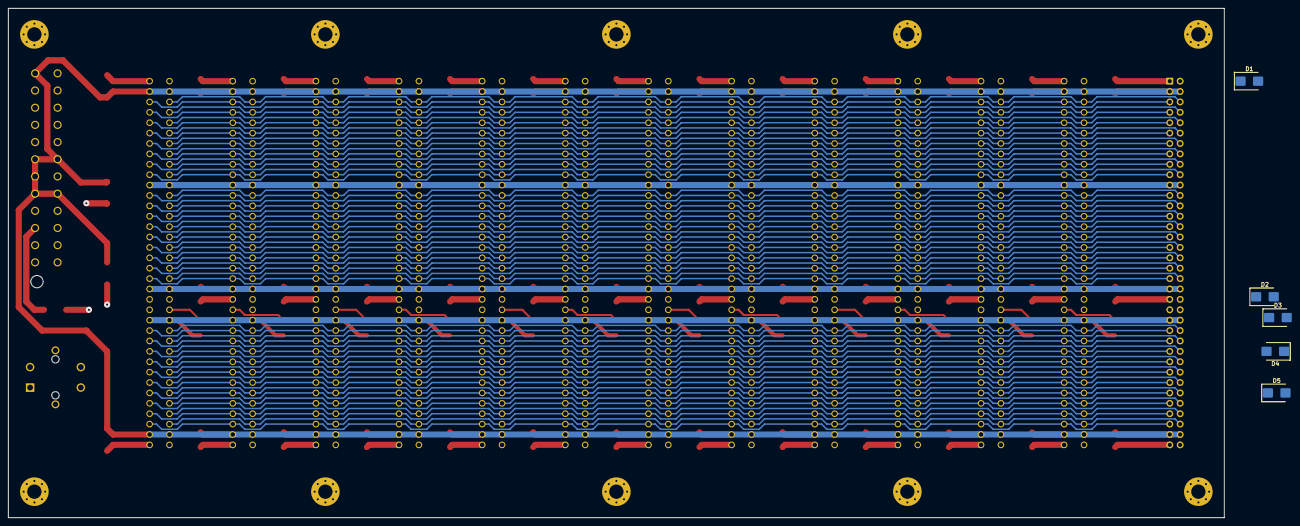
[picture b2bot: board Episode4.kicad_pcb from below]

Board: 4 copper layers, 297.2 x 124.5 mm, 230 parts (5 on the bottom side), 69 nets.

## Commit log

2025-09-10 Initial Comit
2025-09-11 Shuffled thing a bit (visually)
2025-09-12 Added the CPU and Reset sheet
2025-09-12 Cleaned up the drawing, and added some notes
2025-09-12 Moved the library one level up
2025-09-13 Fit both sheets into one
    Instead of having one sheet for reset & CPU, and one for bus buffers, I packed everything in one sheet. And it does not look overpacked.
2025-09-13 Added Arduino Mega to test the circuit. Will be useful for testing the PLDs later
2025-09-24 Added resistor to MIC1232
2025-09-24 Code for virtual NOP tester
2025-09-24 Removed backups
2025-09-25 First commit for episode 3
2025-09-25 Updated paths
2025-09-25 Updating PLD pin assignments
2025-11-16 Pushing back everything, due to PC reinstall.
2025-11-16 Tied up a few loose ends in the PLD page.
2025-11-17 Corrected OE error
2025-11-24 Major updates to PLDs
2025-11-28 Reduced PLDs from 5 to 4, and optimized macrocells to the maximum
2025-11-28 Corrected minor changes in PLDs to reflect Schematic
2025-11-30 Exploited every last macrocells I could.
2025-12-03 Swapped E and IORQ pin on IOdecode
2025-12-04 Issues with PLDs, attempting a workaround
2025-12-10 changed strategy and simplified things
2026-02-07 Massive changes to the PLD code (tested) - Minor changes to the Schematic
2026-02-07 Added datasheet for Flash and RAM
2026-02-07 Preparing the next show, ROM and RAM
2026-02-16 Project Update, change in strategy from breadboard to PCB
2026-02-16 Added traces to the backplane manually.
2026-02-16 SRAM datasheet
2026-02-17 Added more capacitors and extended the bus form 7 to 12
2026-02-17 Worked on BOM
2026-02-18 Changed bus from 62 to 72 pins
2026-02-18 Placed bus traces
2026-02-19 Added various IRQ and FIRQ lines
2026-02-19 Shuffled around IRQ numbers, and removed NMI, as it will by on the CPU card only.
2026-02-20 Changed data trace width, and moving power lanes to inner power plane.
2026-02-20 Reworked bus line order, capacitor and trace placement
2026-02-23 Added some KiCad parts to the library
2026-02-23 Finished the backplane
2026-02-23 Moved power traces from inner CU to back CU
2026-02-23 CPU card initial commit
2026-02-25 Placed Global labels instead. And toying with new PLDs
2026-02-26 Toying with different alternatives for the CPU board
2026-02-28 Finished the preliminary design of the CPU card
2026-02-28 Segmenting Core functionality into multiple cards.
2026-03-01 Toyed with CPU PCB
